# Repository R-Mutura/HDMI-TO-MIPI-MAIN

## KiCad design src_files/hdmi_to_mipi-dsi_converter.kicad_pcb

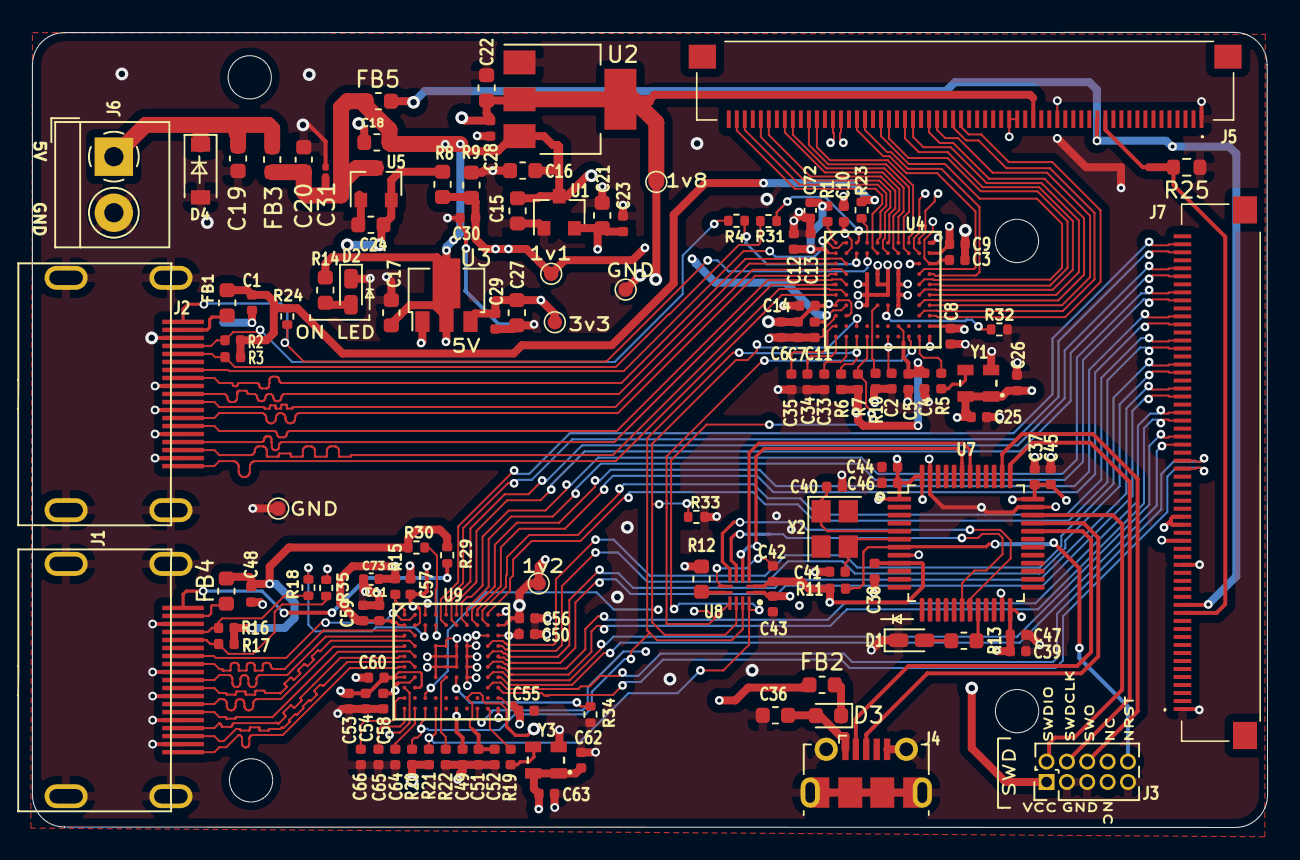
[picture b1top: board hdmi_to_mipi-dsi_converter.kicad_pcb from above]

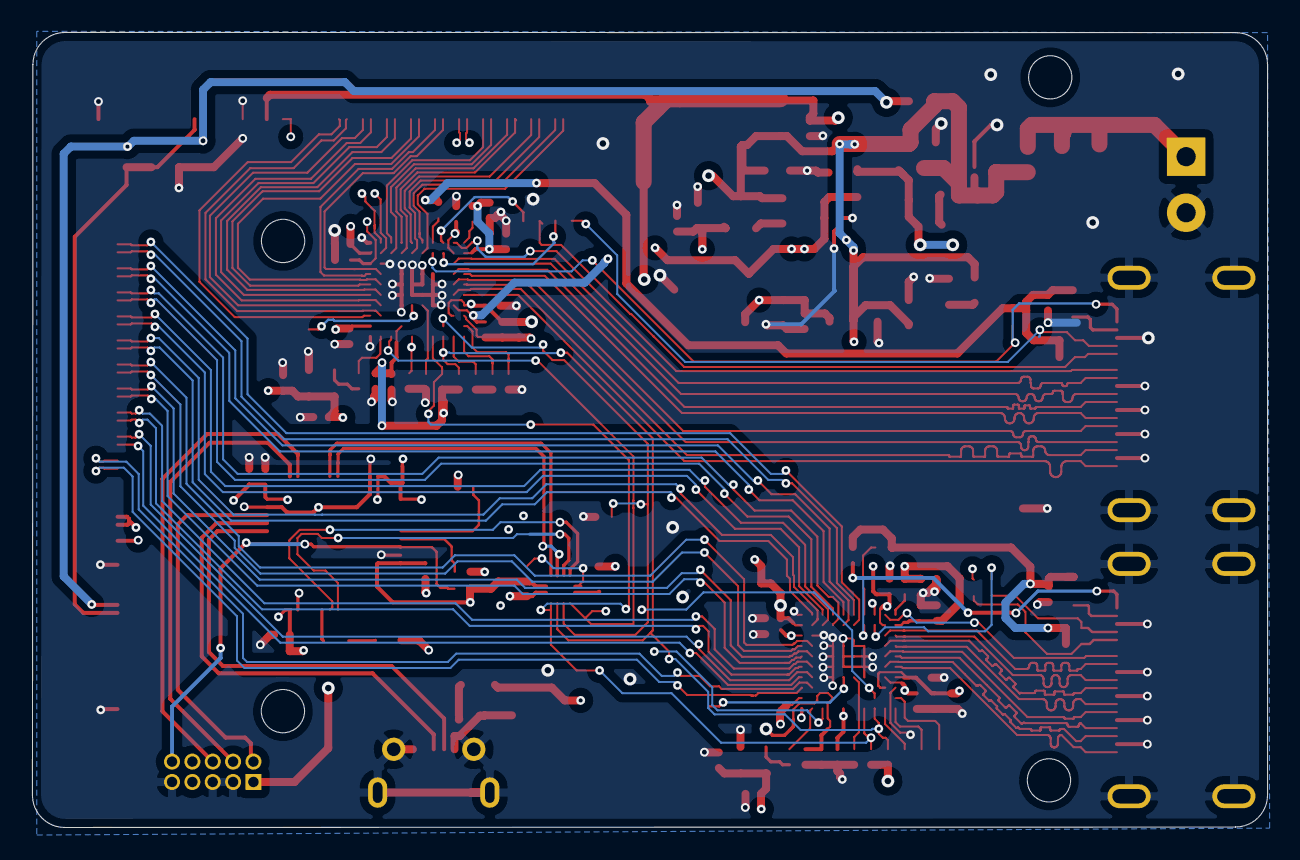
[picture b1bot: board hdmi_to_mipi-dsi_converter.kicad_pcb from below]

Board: 4 copper layers, 77.1 x 49.6 mm, 136 parts (4 on the bottom side), 122 nets.

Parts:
C1, C3, C5, C7, C9, C11, C13, C14, C48, C50, C52, C54, C56, C58, C60, C61: 10n; C_0402_1005Metric
C2, C4, C6, C8, C10, C12, C23, C25, C29, C30, C33, C34, C35, C37, C38, C39, C42, C43, C49, C51, C53, C55, C57, C59, C62, C64, C65, C66: 0.1u; C_0402_1005Metric
C15, C18, C19, C21, C24, C36: 10u; C_0603_1608Metric
C16, C22: 10uF; C_0603_1608Metric
C17, C20: 1uF; C_0603_1608Metric
C26, C63: 0.01u; C_0402_1005Metric
C27: 1u; C_0603_1608Metric
C28: 0.1uF; C_0402_1005Metric
C31: 22uF; R_0201_0603Metric
C40, C41: 18p; C_0402_1005Metric
C44, C45: 10u; C_0402_1005Metric
C46, C47: 4.7u; C_0402_1005Metric
C72, C73: 10nF; C_0402_1005Metric
D1, D2: LED_Small; LED_0603_1608Metric_Castellated
D3: CDBURT0530LL-HF; D_0603_1608Metric
D4: FSV360FP; D_SOD-123
FB1, FB4: Ferrite_Bead_Small; L_0603_1608Metric
FB2: BLM21PG220SN1; L_0603_1608Metric
FB3, FB5: FBMJ1608HS280NTR; L_0603_1608Metric
H1, H2, H3, H4: MountingHole; MountingHole_2.7mm_M2.5
J1, J2: HDMI-019S
J3: Conn_02x05_Odd_Even; PinHeader_2x05_P1.27mm_Vertical
J4: USB_B_Micro; USB_Micro-B_Molex-105017-0001
J5, J7: XF2M60151AH
J6: Conn_01x02; TerminalBlock_4Ucon_1x02_P3.50mm_Horizontal
R1, R15: 2k; R_0402_1005Metric
R2, R3, R16, R17: 47k; R_0402_1005Metric
R4, R18, R31, R35: 33 Ohm; R_0402_1005Metric
R5, R19: 33R; R_0402_1005Metric
R6, R7, R10, R11, R20, R21, R22: 10k; R_0402_1005Metric
R8: 4k; R_0603_1608Metric
R9: 2k; R_0603_1608Metric
R12: 47k; R_0603_1608Metric
R13, R14: 1k; R_0603_1608Metric
R23, R24, R29, R30: 2.2K; R_0402_1005Metric
R25: 0R; R_0603_1608Metric
R32, R34: 10K; R_0402_1005Metric
R33: 47K; R_0402_1005Metric
TP1, TP3, TP4, TP5, TP6, TP7: TestPoint; TestPoint_Pad_D0.9mm
U1: MCP1700-1202E_SOT23; SOT-23
U2: AX1007E18A; SOT-223-3_TabPin2
U3: ME6211A33PG-N; SOT-89-3
U4, U9: TC358870XBG_NOK_; VFBGA-80_7x7mm_Pitch0.65mm
U5: MCP1700-3302E_SOT23; SOT-23
U7: STM32F103C8Tx; LQFP-48_7x7mm_P0.5mm
U8: FXMA2104UMX; QFN40P180X180X55-12N
Y1, Y3: CRYSTAL_48MHZ; DSC6101JI2A-048.0000
Y2: 8MHz; Crystal_SMD_3225-4Pin_3.2x2.5mm

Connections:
+1V1: C2.1, C3.1, C10.1, C11.1, C30.1, C49.1, C50.1, C57.1, C58.1, R8.2, R9.1, TP5.1, U4.B2, U4.C10, U4.G2, U4.K6, U9.B2, U9.C10, U9.G2, U9.K6
+1V2: C8.1, C9.1, C21.1, C23.1, C55.1, C56.1, TP7.1, U1.2, U4.B10, U4.J10, U9.B10, U9.J10
+1V8: C4.1, C5.1, C22.1, C28.1, C43.1, C51.1, C52.1, J5.22, J7.22, R6.2, R7.2, R20.2, R21.2, TP6.1, U2.2, U4.J7, U8.1, U9.J7
+3V3: C6.1, C7.1, C12.1, C13.1, C14.1, C25.1, C26.1, C27.1, C29.1, C37.1, C38.1, C39.1, C42.1, C44.1, C45.1, C46.1, C47.1, C53.1, C54.1, C59.1, C60.1, C61.1, C62.1, C63.1, C72.1, C73.1, J3.1, J5.24, J5.25, J7.24, J7.25, R1.2, R11.1, R12.2, R15.2, TP1.1, U3.3, U4.B1, U4.G1, U4.H2, U7.1, U7.9, U7.24, U7.36, U7.48, U8.2, U9.B1, U9.G1, U9.H2, Y1.1, Y1.4, Y3.1, Y3.4
+5V: C15.1, C16.1, C17.1, C18.1, C20.1, C31.1, FB2.1, FB3.1, FB5.2, R14.1, U1.3, U2.3, U3.2, U5.3
/CDSI0_TX_D0_N: J5.32, U4.H9
/CDSI0_TX_D0_P: J5.31, U4.H10
/CDSI0_TX_D1_N: J5.35, U4.G9
/CDSI0_TX_D1_P: J5.34, U4.G10
/CDSI0_TX_D2_N: J5.41, U4.E9
/CDSI0_TX_D2_P: J5.40, U4.E10
/CDSI0_TX_D3_N: J5.44, U4.D9
/CDSI0_TX_D3_P: J5.43, U4.D10
/CDSI0_TX_DC_N: J5.38, U4.F9
/CDSI0_TX_DC_P: J5.37, U4.F10
/CDSI1_TX_D0_N: J5.47, U4.B9
/CDSI1_TX_D0_P: J5.46, U4.A9
/CDSI1_TX_D1_N: J5.50, U4.B8
/CDSI1_TX_D1_P: J5.49, U4.A8
/CDSI1_TX_D2_N: J5.56, U4.B6
/CDSI1_TX_D2_P: J5.55, U4.A6
/CDSI1_TX_D3_N: J5.59, U4.B5
/CDSI1_TX_D3_P: J5.58, U4.A5
/CDSI1_TX_DC_N: J5.53, U4.B7
/CDSI1_TX_DC_P: J5.52, U4.A7
/CEC_OUT: J2.13, U4.A2
/DDC_SCL: J2.15, R3.1, R31.2
/DDC_SDA: J2.16, R2.1, R4.2
/HDMIC_N: J2.12, U4.C2
/HDMIC_P: J2.10, U4.C1
/HDMID0_N: J2.9, U4.D2
/HDMID0_P: J2.7, U4.D1
/HDMID1_N: J2.6, U4.E2
/HDMID1_P: J2.4, U4.E1
/HDMID2_N: J2.3, U4.F2
/HDMID2_P: J2.1, U4.F1
/HDMI_5V: C1.1, FB1.2, R2.2, R3.2, R23.1, R24.2
/HDMI_HPD0: J2.19, R24.1, U4.B4
/HPDI: R23.2, U4.A4
/hdmi_mipi_2/CDSI0_TX_D0_N: J7.32, U9.H9
/hdmi_mipi_2/CDSI0_TX_D0_P: J7.31, U9.H10
/hdmi_mipi_2/CDSI0_TX_D1_N: J7.35, U9.G9
/hdmi_mipi_2/CDSI0_TX_D1_P: J7.34, U9.G10
/hdmi_mipi_2/CDSI0_TX_D2_N: J7.41, U9.E9
/hdmi_mipi_2/CDSI0_TX_D2_P: J7.40, U9.E10
/hdmi_mipi_2/CDSI0_TX_D3_N: J7.44, U9.D9
/hdmi_mipi_2/CDSI0_TX_D3_P: J7.43, U9.D10
/hdmi_mipi_2/CDSI0_TX_DC_N: J7.38, U9.F9
/hdmi_mipi_2/CDSI0_TX_DC_P: J7.37, U9.F10
/hdmi_mipi_2/CDSI1_TX_D0_N: J7.47, U9.B9
/hdmi_mipi_2/CDSI1_TX_D0_P: J7.46, U9.A9
/hdmi_mipi_2/CDSI1_TX_D1_N: J7.50, U9.B8
/hdmi_mipi_2/CDSI1_TX_D1_P: J7.49, U9.A8
/hdmi_mipi_2/CDSI1_TX_D2_N: J7.56, U9.B6
/hdmi_mipi_2/CDSI1_TX_D2_P: J7.55, U9.A6
/hdmi_mipi_2/CDSI1_TX_D3_N: J7.59, U9.B5
/hdmi_mipi_2/CDSI1_TX_D3_P: J7.58, U9.A5
/hdmi_mipi_2/CDSI1_TX_DC_N: J7.53, U9.B7
/hdmi_mipi_2/CDSI1_TX_DC_P: J7.52, U9.A7
/hdmi_mipi_2/CEC_OUT: J1.13, U9.A2
/hdmi_mipi_2/DDC_SCL: J1.15, R17.1, R35.2
/hdmi_mipi_2/DDC_SDA: J1.16, R16.2, R18.2
/hdmi_mipi_2/HDMIC_N: J1.12, U9.C2
/hdmi_mipi_2/HDMIC_P: J1.10, U9.C1
/hdmi_mipi_2/HDMID0_N: J1.9, U9.D2
/hdmi_mipi_2/HDMID0_P: J1.7, U9.D1
/hdmi_mipi_2/HDMID1_N: J1.6, U9.E2
/hdmi_mipi_2/HDMID1_P: J1.4, U9.E1
/hdmi_mipi_2/HDMID2_N: J1.3, U9.F2
/hdmi_mipi_2/HDMID2_P: J1.1, U9.F1
/hdmi_mipi_2/HDMI_5V: C48.1, FB4.2, R16.1, R17.2, R29.2, R30.1
/hdmi_mipi_2/HDMI_HPDO: J1.19, R29.1, U9.B4
/hdmi_mipi_2/HPDI: R30.2, U9.A4
/hdmi_mipi_2/refclk: R19.1, U9.K9
/hdmi_mipi_2/test: R22.2, U9.G5
/mcu_ctrl/DIFF_N: J4.2, U7.32
/mcu_ctrl/DIFF_P: J4.3, U7.33
/mcu_ctrl/INT: U7.18, U8.5
/mcu_ctrl/LED: R13.1, U7.20
/mcu_ctrl/NRST: J3.10, R11.2, U7.7
/mcu_ctrl/OSCIN: C40.1, U7.5, Y2.1
/mcu_ctrl/OSCOUT: C41.1, U7.6, Y2.3
/mcu_ctrl/RST: U7.19, U8.6
/mcu_ctrl/SCL: U7.42, U8.3
/mcu_ctrl/SDA: U7.43, U8.4
/mcu_ctrl/SWDCLK: J3.4, U7.37
/mcu_ctrl/SWDIO: J3.2, U7.34
/mcu_ctrl/SWO: J3.6, U7.38
/power/5V_IN: C19.1, D4.1, FB3.2, J6.1
/refclk: R5.1, U4.K9
/test: R10.2, U4.G5
CTRL_INT: R33.1, U4.J3, U8.10, U9.J3
GND: C1.2, C2.2, C3.2, C4.2, C5.2, C6.2, C7.2, C8.2, C9.2, C10.2, C11.2, C12.2, C13.2, C14.2, C15.2, C16.2, C17.2, C18.2, C19.2, C20.2, C21.2, C22.2, C23.2, C24.2, C25.2, C26.2, C27.2, C28.2, C29.2, C30.2, C31.2, C33.2, C34.2, C35.2, C36.2, C37.2, C38.2, C39.2, C40.2, C41.2, C42.2, C43.2, C44.2, C45.2, C46.2, C47.2, C48.2, C49.2, C50.2, C51.2, C52.2, C53.2, C54.2, C55.2, C56.2, C57.2, C58.2, C59.2, C60.2, C61.2, C62.2, C63.2, C64.2, C65.2, C66.2, C72.2, C73.2, D1.1, D2.1, D4.2, J1.2, J1.5, J1.8, J1.11, J1.17, J1.SH, J2.2, J2.5, J2.8, J2.11, J2.17, J2.SH, J3.3, J3.5, J3.9, J4.5, J4.6, J5.1, J5.19, J6.2, J7.1, J7.19, R9.2, R10.1, R22.1, R25.1, R32.1, R33.2, R34.1, TP3.1, TP4.1, U1.1, U2.1, U3.1, U4.A10, U4.C9, U4.D4, U4.D5, U4.D6, U4.D7, U4.E4, U4.E5, U4.E6, U4.E7, U4.F4, U4.F5, U4.F6, U4.F7, U4.G4, U4.G7, U4.H1, U4.K10, U5.1, U7.8, U7.23, U7.35, U7.47, U8.7, U9.A10, U9.C9, U9.D4, U9.D5, U9.D6, U9.D7, U9.E4, U9.E5, U9.E6, U9.E7, U9.F4, U9.F5, U9.F6, U9.F7, U9.G4, U9.G7, U9.H1, U9.K10, Y1.2, Y3.2
I2C_SCL: R7.1, R21.1, U4.K4, U8.12, U9.K4
I2C_SDA: R6.1, R20.1, U4.K3, U8.11, U9.K3
unnamed: C24.1, R8.1, U5.2
unnamed: C33.1, U4.K2
unnamed: C34.1, U4.K1
unnamed: C35.1, U4.J1
unnamed: C64.1, U9.K2
unnamed: C65.1, U9.K1
unnamed: C66.1, U9.J1
unnamed: D1.2, R13.2
unnamed: D2.2, R14.2
unnamed: D3.1, FB2.2
unnamed: FB1.1, J2.18
unnamed: FB4.1, J1.18
unnamed: R1.1, U4.A1
unnamed: R4.1, U4.B3
unnamed: R5.2, Y1.3
unnamed: R12.1, U8.8
unnamed: R15.1, U9.A1
unnamed: R18.1, U9.B3
unnamed: R19.2, Y3.3
unnamed: R31.1, U4.A3
unnamed: R32.2, U4.G6
unnamed: R34.2, U9.G6
unnamed: R35.1, U9.A3
RESET_N: U4.K8, U8.9, U9.K8
VBUS: C36.1, D3.2, J4.1
VSN: J5.13, J7.13, R25.2
VSP: FB5.1, J5.14, J7.14

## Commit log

2021-11-18 new commits>>layout complete and proper...BOM awaiting
2021-11-19 updated all files and production files as well
2021-12-01 reduced form factor
2021-12-23 update on HDMI to MIPI
2021-12-23 update on the hdmi to mipi

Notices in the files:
parts and their libraries:
Copyright 2016 Accelerated Designs. All rights reserved.
